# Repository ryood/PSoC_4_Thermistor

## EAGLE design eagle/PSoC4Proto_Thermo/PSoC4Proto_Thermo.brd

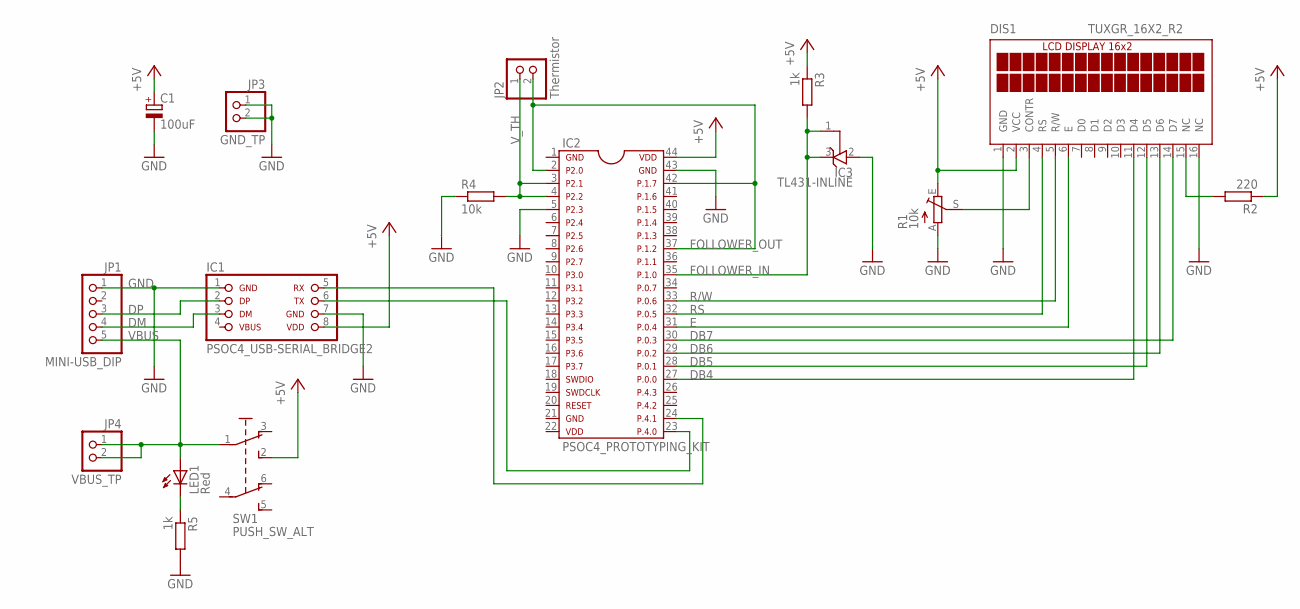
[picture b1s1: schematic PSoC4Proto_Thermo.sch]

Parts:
C1: 100uF; E2,5-7
DIS1: TUXGR_16X2_R2
IC1: PSOC4_USB-SERIAL_BRIDGE2; PSOC4-PROTO_USB-SERIAL_BRIDGE
IC2: PSOC4_PROTOTYPING_KIT; DIL44-8
IC3: TL431-INLINE; TO226AA
JP1: MINI-USB_DIP
JP2: Thermistor; 1X02
JP3: GND_TP; 1X02
JP4: VBUS_TP; 1X02
LED1: Red; LED3MM
R1: 10k; B25P
R2: 220; 0207/7
R3, R5: 1k; 0207/7
R4: 10k; 0207/7
SW1: PUSH_SW_ALT

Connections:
+5V: C1.+, DIS1.2 (VCC), IC1.8, IC2.44, R1.E, R2.1, R3.1, SW1.2 (S)
DB4: DIS1.11 (D4), IC2.27
DB5: DIS1.12 (D5), IC2.28
DB6: DIS1.13 (D6), IC2.29
DB7: DIS1.14 (D7), IC2.30
DM: IC1.3, JP1.4
DP: IC1.2, JP1.3
E: DIS1.6 (E), IC2.31
FOLLOWER_IN: IC2.35, IC3.1 (R), IC3.3 (C), R3.2
FOLLOWER_OUT: IC2.2, IC2.37, IC2.42, JP2.2
GND: C1.-, DIS1.1 (GND), DIS1.16 (NC), IC1.1, IC1.7, IC2.5, IC2.43, IC3.2 (A), JP1.1, JP3.1, JP3.2, R1.A, R4.1, R5.2
unnamed: DIS1.15 (NC), R2.2
unnamed: DIS1.3 (CONTR), R1.S
unnamed: LED1.K (C), R5.1
R/W: DIS1.5 (R/W), IC2.33
RS: DIS1.4 (RS), IC2.32
RX: IC1.5, IC2.24
TX: IC1.6, IC2.23
VBUS: JP1.5, JP4.1, JP4.2, LED1.A, SW1.1
V_TH: IC2.3, IC2.4, JP2.1, R4.2

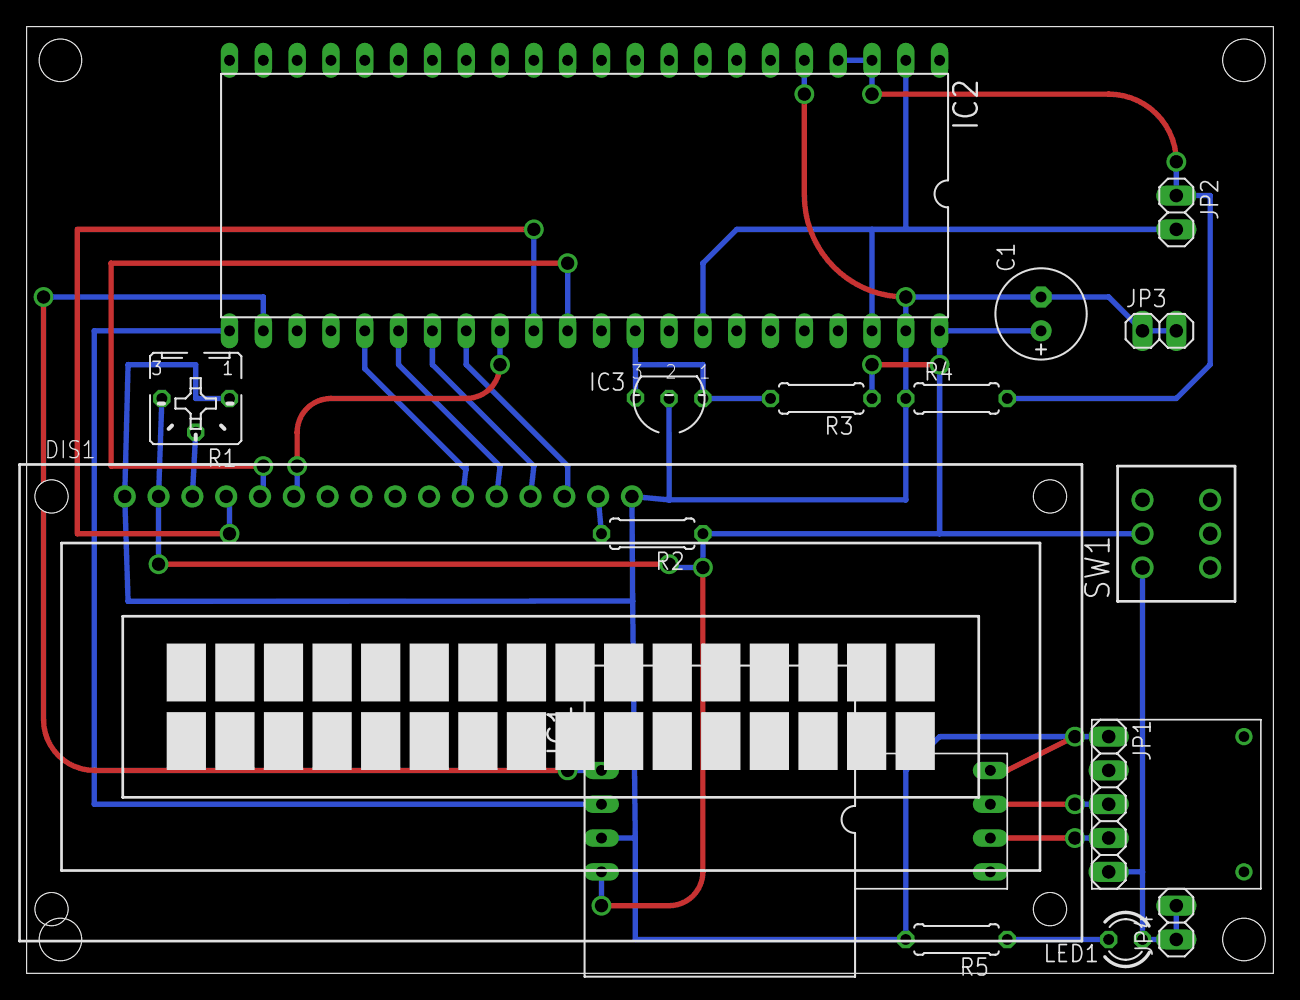
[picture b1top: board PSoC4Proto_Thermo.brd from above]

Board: 2 copper layers, 93.7 x 71.1 mm, 16 parts (0 on the bottom side), 20 nets.

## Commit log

2016-09-22 Split ThemistorCalc's temperature range
2016-09-24 Add: Char LCD Display
2016-09-24 Add: Project for Prototyping Kit
2016-12-06 Add: Eagle files
2016-12-14 Update: Eagle files
2016-12-14 Add: Test Chart
2017-01-16 Change the Interval to 1s. LCD display degree char.
